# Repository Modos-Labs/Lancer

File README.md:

Lancer is the codename of our EPD laptop prototype.

# Specifications

The specification listed are preliminary and subject to change.

- SoC: Amlogic S922X (4x Cortex-A73 @ 2.2 GHz + 2x Cortex-A53 @ 2.0 GHz)
- RAM: 4GB DDR4 32bit
- SSD: User-replaceable M.2 SSD
- Network: 802.11n + BT4.0
- Screen: 13.3" 1600x1200 E-paper display via Caster EPDC (over MIPI DSI)
- Battery: Compatible with T4x battery
- Ports:
  - USB 2.0 Type-A Host x2
  - USB 2.0 Micro-B Device
  - USB Serial (Micro-B)
  - 10/100Mbps Ethernet
  - 3.5 mm Headphone Jack
  - 3.5 mm Line-In Jack
  - HDMI Output

# License

The hardware design is released under the CERN Open Source Hardware License strongly-reciprocal variant, CERN-OHL-S. A copy of the license is provided in the source repository. Additionally, user guide of the license is provided on ohwr.org.

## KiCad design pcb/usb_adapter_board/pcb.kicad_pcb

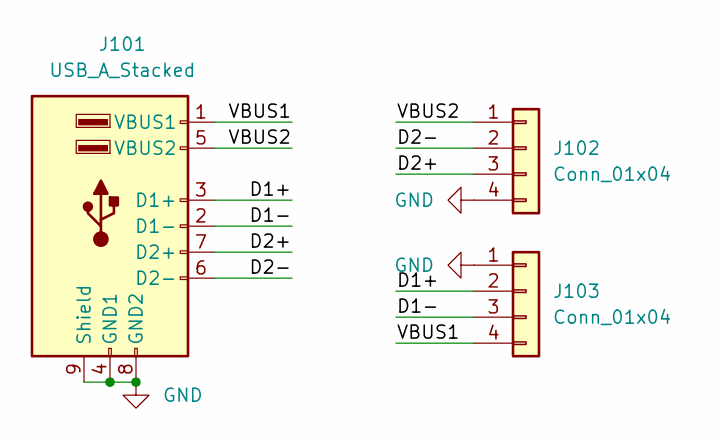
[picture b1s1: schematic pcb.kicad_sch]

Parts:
J101: USB_A_Stacked; USB_A_Wuerth_614008235023_Vertical_Stacked
J102, J103: Conn_01x04; PinHeader_1x04_P1.27mm_Horizontal_Alt

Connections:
/D1+: J101.3 (D1+), J103.2
/D1-: J101.2 (D1-), J103.3
/D2+: J101.7 (D2+), J102.3
/D2-: J101.6 (D2-), J102.2
/VBUS1: J101.1 (VBUS1), J103.4
/VBUS2: J101.5 (VBUS2), J102.1
GND: J101.4 (GND1), J101.8 (GND2), J101.9 (Shield), J102.4, J103.1

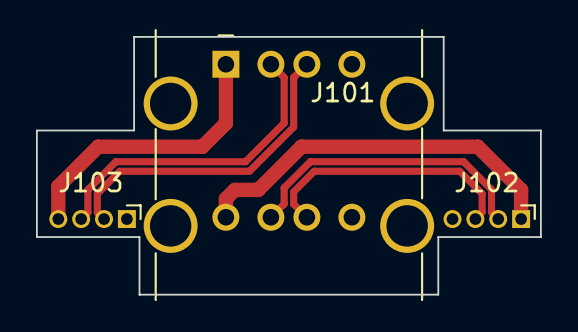
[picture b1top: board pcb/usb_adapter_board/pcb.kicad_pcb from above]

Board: 2 copper layers, 28.0 x 14.3 mm, 3 parts (0 on the bottom side), 7 nets.

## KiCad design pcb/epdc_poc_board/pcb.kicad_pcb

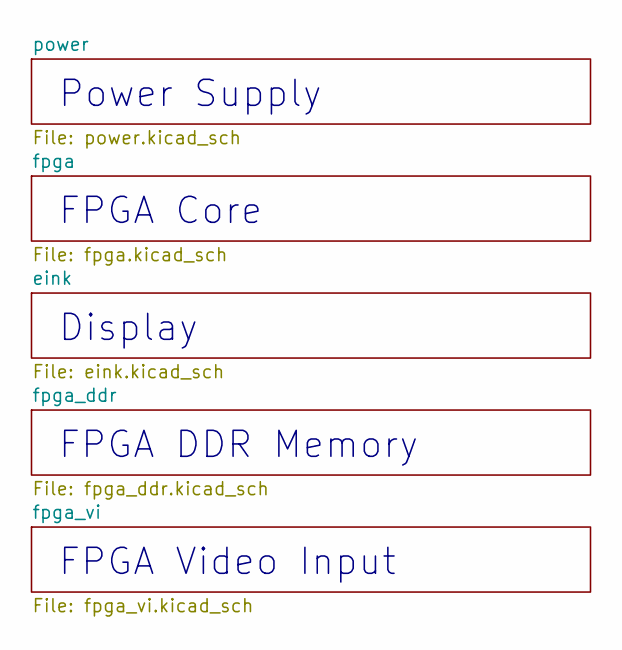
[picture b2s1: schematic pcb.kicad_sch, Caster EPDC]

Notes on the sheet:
Power Supply
FPGA Core
Display
FPGA DDR Memory
FPGA Video Input

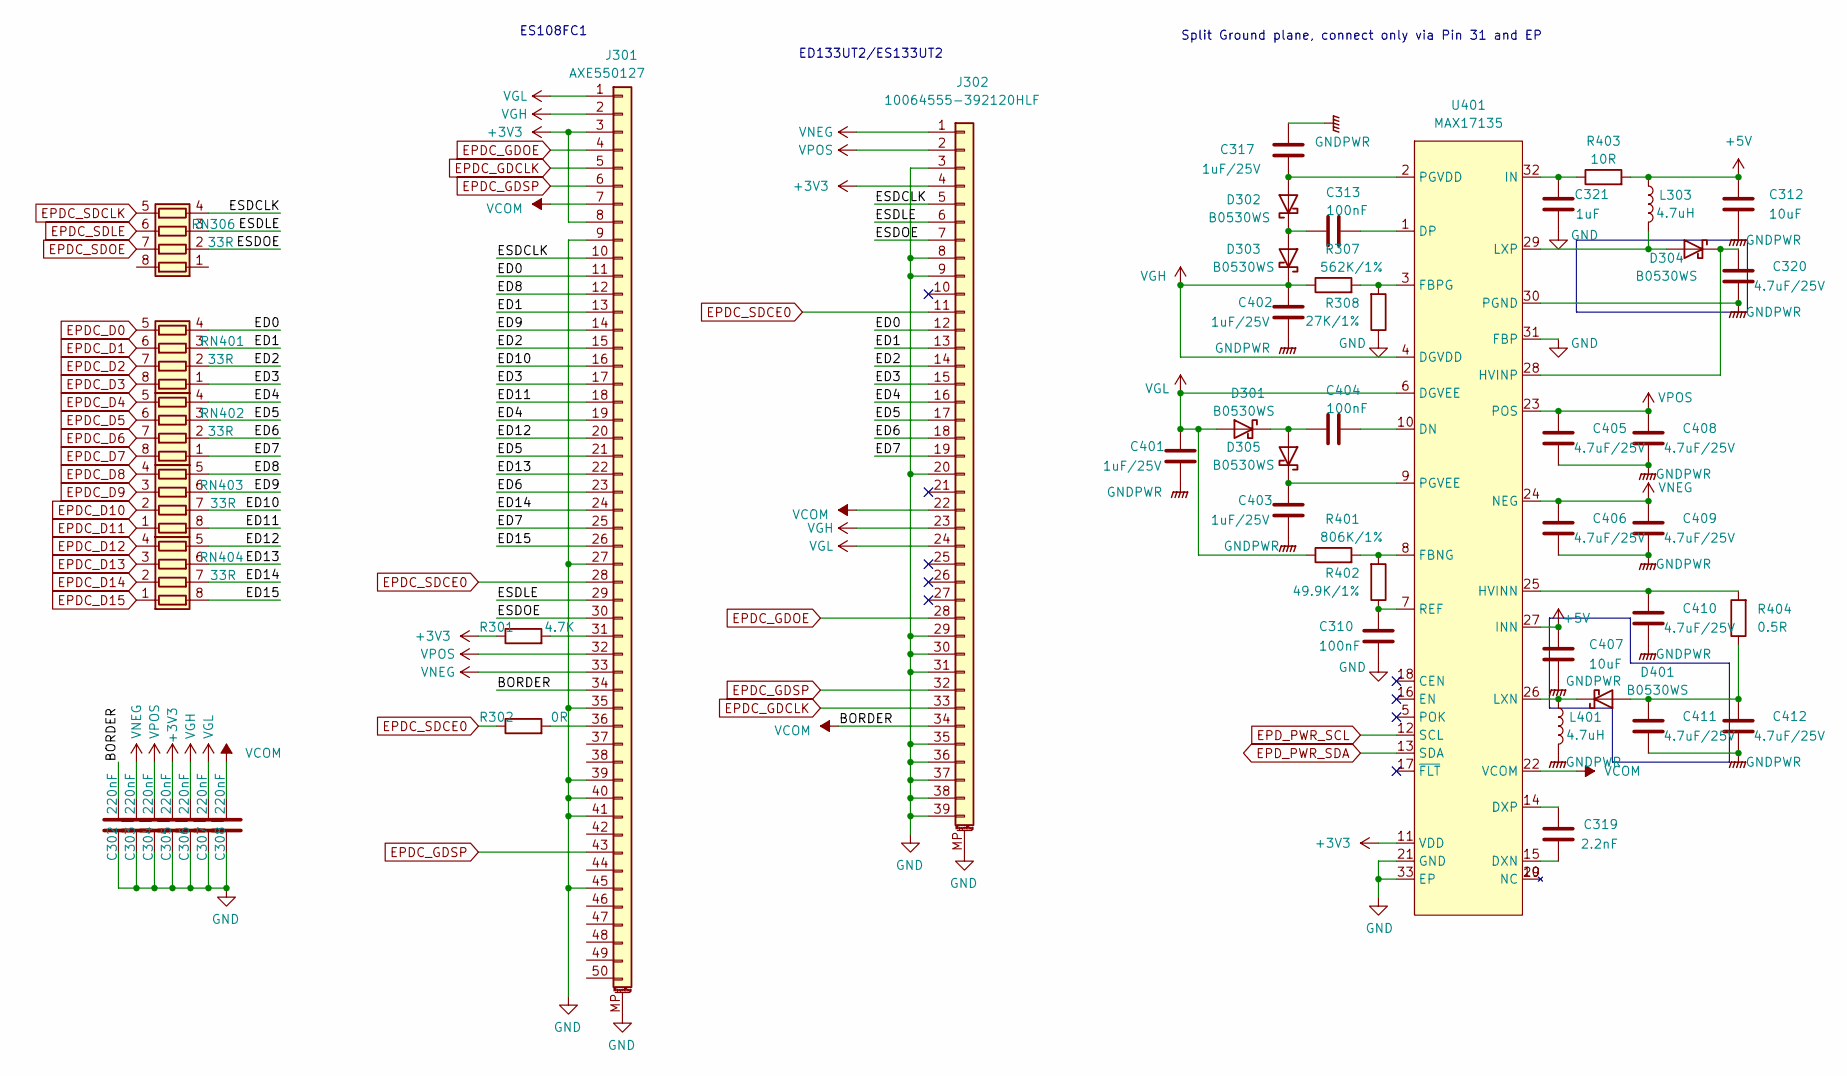
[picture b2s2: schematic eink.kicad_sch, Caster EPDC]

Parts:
C302, C303, C304, C305, C306, C307, C308: 220nF; C_0402_1005Metric; LCSC C880414
C310, C313, C404: 100nF; C_0402_1005Metric; LCSC C56392
C312, C407: 10uF; C_0603_1608Metric; LCSC C105490
C317, C401, C402, C403: 1uF/25V; C_0805_2012Metric; LCSC C111769
C319: 2.2nF; C_0402_1005Metric; LCSC C913886
C320, C405, C406, C408, C409, C410, C411, C412: 4.7uF/25V; C_0805_2012Metric; LCSC C105489
C321: 1uF; C_0402_1005Metric; LCSC C157353
D301, D302, D303, D304, D305, D401: B0530WS; D_SOD-323; LCSC C475612
J301: AXE550127
J302: 10064555-392120HLF; FCI_10064555-392120HLF; LCSC 609-10064555-392120HLFCT-ND
L303, L401: 4.7uH; L_1212; LCSC C340379
R301: 4.7K; R_0402_1005Metric; LCSC C105870
R302: 0R; R_0402_1005Metric; LCSC C60485
R307: 562K/1%; R_0402_1005Metric; LCSC C273337
R308: 27K/1%; R_0402_1005Metric; LCSC C138022
R401: 806K/1%; R_0402_1005Metric; LCSC C375495
R402: 49.9K/1%; R_0402_1005Metric; LCSC C137969
R403: 10R; R_0402_1005Metric; LCSC C137925
R404: 0.5R; R_0603_1608Metric; LCSC C45312
RN306, RN401, RN402, RN403, RN404: 33R; R_Array_Convex_4x0402; LCSC C148513
U401: MAX17135; QFN-32-1EP_5x5mm_P0.5mm_EP3.1x3.1mm_ThermalVias

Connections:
+3V3: C305.1, J301.3, J301.8, J302.4, R301.1, U401.11 (VDD); also elsewhere on the board
+5V: C312.2, C407.2, L303.1, R403.2, U401.27 (INN); also elsewhere on the board
/eink/ED0: J301.11, J302.12, RN401.4 (R4.1)
/eink/ED1: J301.13, J302.13, RN401.3 (R3.1)
/eink/ED2: J301.15, J302.14, RN401.2 (R2.1)
/eink/ED3: J301.17, J302.15, RN401.1 (R1.1)
/eink/ED4: J301.19, J302.16, RN402.4 (R4.1)
/eink/ED5: J301.21, J302.17, RN402.3 (R3.1)
/eink/ED6: J301.23, J302.18, RN402.2 (R2.1)
/eink/ED7: J301.25, J302.19, RN402.1 (R1.1)
/eink/ED8: J301.12, RN403.5 (R4.2)
/eink/ED9: J301.14, RN403.6 (R3.2)
/eink/ED10: J301.16, RN403.7 (R2.2)
/eink/ED11: J301.18, RN403.8 (R1.2)
/eink/ED12: J301.20, RN404.5 (R4.2)
/eink/ED13: J301.22, RN404.6 (R3.2)
/eink/ED14: J301.24, RN404.7 (R2.2)
/eink/ED15: J301.26, RN404.8 (R1.2)
/eink/ESDCLK: J301.10, J302.5, RN306.4 (R4.1)
/eink/ESDLE: J301.29, J302.6, RN306.3 (R3.1)
/eink/ESDOE: J301.30, J302.7, RN306.2 (R2.1)
EPDC_D0: RN401.5 (R4.2); also elsewhere on the board
EPDC_D1: RN401.6 (R3.2); also elsewhere on the board
EPDC_D2: RN401.7 (R2.2); also elsewhere on the board
EPDC_D3: RN401.8 (R1.2); also elsewhere on the board
EPDC_D4: RN402.5 (R4.2); also elsewhere on the board
EPDC_D5: RN402.6 (R3.2); also elsewhere on the board
EPDC_D6: RN402.7 (R2.2); also elsewhere on the board
EPDC_D7: RN402.8 (R1.2); also elsewhere on the board
EPDC_D8: RN403.4 (R4.1); also elsewhere on the board
EPDC_D9: RN403.3 (R3.1); also elsewhere on the board
EPDC_D10: RN403.2 (R2.1); also elsewhere on the board
EPDC_D11: RN403.1 (R1.1); also elsewhere on the board
EPDC_D12: RN404.4 (R4.1); also elsewhere on the board
EPDC_D13: RN404.3 (R3.1); also elsewhere on the board
EPDC_D14: RN404.2 (R2.1); also elsewhere on the board
EPDC_D15: RN404.1 (R1.1); also elsewhere on the board
EPDC_GDCLK: J301.5, J302.33; also elsewhere on the board
EPDC_GDOE: J301.4, J302.28; also elsewhere on the board
EPDC_GDSP: J301.6, J301.43, J302.32; also elsewhere on the board
EPDC_SDCE0: J301.28, J302.11, R302.1; also elsewhere on the board
EPDC_SDCLK: RN306.5 (R4.2); also elsewhere on the board
EPDC_SDLE: RN306.6 (R3.2); also elsewhere on the board
EPDC_SDOE: RN306.7 (R2.2); also elsewhere on the board
EPD_PWR_SCL: U401.12 (SCL); also elsewhere on the board
EPD_PWR_SDA: U401.13 (SDA); also elsewhere on the board
GND: C302.2, C303.2, C304.2, C305.2, C306.2, C307.2, C308.2, C310.1, C321.1, J301.9, J301.27, J301.35, J301.39, J301.40, J301.41, J301.45, J301.MP (MountPin), J302.3, J302.8, J302.9, J302.20, J302.29, J302.30, J302.31, J302.35, J302.36, J302.37, J302.38, J302.39, J302.MP (MountPin), R308.1, U401.21 (GND), U401.31 (FBP), U401.33 (EP); also elsewhere on the board
GNDPWR: C312.1, C317.2, C320.1, C401.1, C402.1, C403.1, C405.1, C406.1, C407.1, C408.1, C409.1, C410.1, C411.1, C412.1, L401.2, U401.30 (PGND)
unnamed: C310.2, R402.1, U401.7 (REF)
unnamed: C313.1, D302.1 (K), D303.2 (A)
unnamed: C313.2, U401.1 (DP)
unnamed: C317.1, D302.2 (A), U401.2 (PGVDD)
unnamed: C319.1, U401.15 (DXN)
unnamed: C319.2, U401.14 (DXP)
unnamed: C320.2, D304.1 (K), U401.28 (HVINP)
unnamed: C321.2, R403.1, U401.32 (IN)
unnamed: C403.2, D305.1 (K), U401.9 (PGVEE)
unnamed: C404.1, D301.1 (K), D305.2 (A)
unnamed: C404.2, U401.10 (DN)
unnamed: C410.2, R404.2, U401.25 (HVINN)
unnamed: C411.2, C412.2, D401.2 (A), R404.1
unnamed: D304.2 (A), L303.2, U401.29 (LXP)
unnamed: D401.1 (K), L401.1, U401.26 (LXN)
unnamed: J301.31, R301.2
unnamed: J301.36, R302.2
unnamed: R307.2, R308.2, U401.3 (FBPG)
unnamed: R401.2, R402.2, U401.8 (FBNG)
VCOM: C302.1, C308.1, J301.7, J301.34, J302.22, J302.34, U401.22 (VCOM)
VGH: C306.1, C402.2, D303.1 (K), J301.2, J302.23, R307.1, U401.4 (DGVDD)
VGL: C307.1, C401.2, D301.2 (A), J301.1, J302.24, R401.1, U401.6 (DGVEE)
VNEG: C303.1, C406.2, C409.2, J301.33, J302.1, U401.24 (NEG)
VPOS: C304.1, C405.2, C408.2, J301.32, J302.2, U401.23 (POS)

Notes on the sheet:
ES108FC1
ED133UT2/ES133UT2
Split Ground plane, connect only via Pin 31 and EP

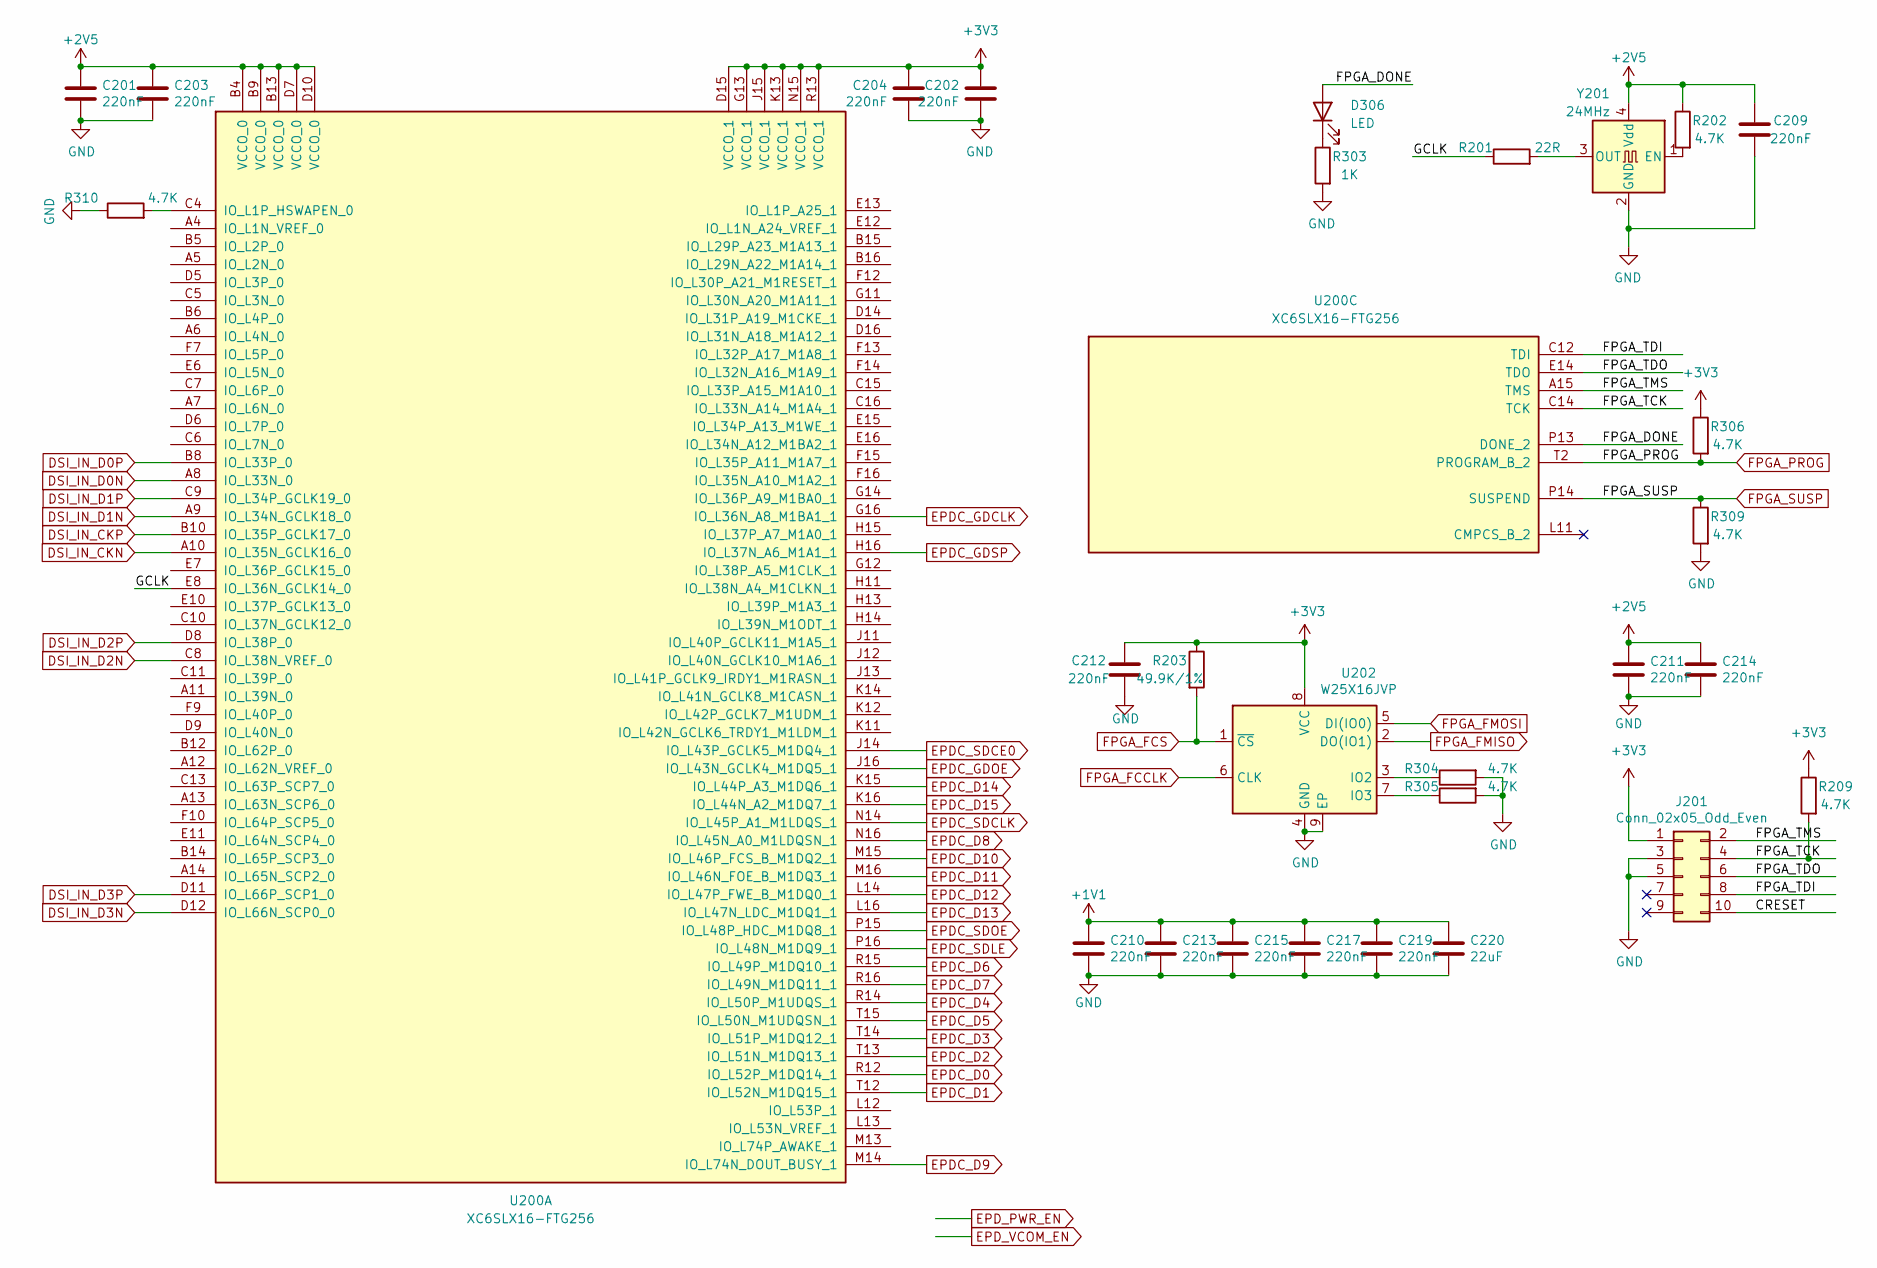
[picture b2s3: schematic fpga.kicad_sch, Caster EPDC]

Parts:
C201, C202, C203, C204, C209, C210, C211, C212, C213, C214, C215, C217, C219: 220nF; C_0402_1005Metric; LCSC C880414
C220: 22uF; C_0603_1608Metric; LCSC C94018
D306: LED; LED_0603_1608Metric; LCSC C90692
J201: Conn_02x05_Odd_Even; PinHeader_2x05_P1.27mm_Vertical_SMD
R201: 22R; R_0402_1005Metric; LCSC C93929
R202, R209, R304, R305, R306, R309, R310: 4.7K; R_0402_1005Metric; LCSC C105870
R203: 49.9K/1%; R_0402_1005Metric; LCSC C137969
R303: 1K; R_0402_1005Metric; LCSC C105637
U200: XC6SLX16-FTG256; BGA-256_14.0x14.0mm_Layout16x16_P0.8mm_Ball0.45mm_Pad0.32mm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; LCSC C39313
U202: W25X16JVP; WSON-8-1EP_6x5mm_P1.27mm_EP3.4x4.3mm; LCSC C571260
Y201: 24MHz; Oscillator_SMD_Abracon_ASE-4Pin_3.2x2.5mm; LCSC C252339

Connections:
+1V1: C210.1, C213.1, C215.1, C217.1, C219.1, C220.1; also elsewhere on the board
+2V5: C201.1, C203.1, C209.2, C211.1, C214.1, R202.1, U200.B4 (VCCO_0), U200.B9 (VCCO_0), U200.B13 (VCCO_0), U200.D7 (VCCO_0), U200.D10 (VCCO_0), Y201.4 (Vdd); also elsewhere on the board
+3V3: C202.1, C204.1, C212.2, J201.1, R203.1, R209.1, R306.1, U200.D15 (VCCO_1), U200.G13 (VCCO_1), U200.J15 (VCCO_1), U200.K13 (VCCO_1), U200.N15 (VCCO_1), U200.R13 (VCCO_1), U202.8 (VCC); also elsewhere on the board
/fpga/CRESET: J201.10
/fpga/FPGA_DONE: D306.2 (A), U200.P13 (DONE_2)
/fpga/FPGA_TCK: J201.4, R209.2, U200.C14 (TCK)
/fpga/FPGA_TDI: J201.8, U200.C12 (TDI)
/fpga/FPGA_TDO: J201.6, U200.E14 (TDO)
/fpga/FPGA_TMS: J201.2, U200.A15 (TMS)
/fpga/GCLK: R201.1, U200.E8 (IO_L36N_GCLK14_0)
DSI_IN_CKN: U200.A10 (IO_L35N_GCLK16_0); also elsewhere on the board
DSI_IN_CKP: U200.B10 (IO_L35P_GCLK17_0); also elsewhere on the board
DSI_IN_D0N: U200.A8 (IO_L33N_0); also elsewhere on the board
DSI_IN_D0P: U200.B8 (IO_L33P_0); also elsewhere on the board
DSI_IN_D1N: U200.A9 (IO_L34N_GCLK18_0); also elsewhere on the board
DSI_IN_D1P: U200.C9 (IO_L34P_GCLK19_0); also elsewhere on the board
DSI_IN_D2N: U200.C8 (IO_L38N_VREF_0); also elsewhere on the board
DSI_IN_D2P: U200.D8 (IO_L38P_0); also elsewhere on the board
DSI_IN_D3N: U200.D12 (IO_L66N_SCP0_0); also elsewhere on the board
DSI_IN_D3P: U200.D11 (IO_L66P_SCP1_0); also elsewhere on the board
EPDC_D0: U200.R12 (IO_L52P_M1DQ14_1); also elsewhere on the board
EPDC_D1: U200.T12 (IO_L52N_M1DQ15_1); also elsewhere on the board
EPDC_D2: U200.T13 (IO_L51N_M1DQ13_1); also elsewhere on the board
EPDC_D3: U200.T14 (IO_L51P_M1DQ12_1); also elsewhere on the board
EPDC_D4: U200.R14 (IO_L50P_M1UDQS_1); also elsewhere on the board
EPDC_D5: U200.T15 (IO_L50N_M1UDQSN_1); also elsewhere on the board
EPDC_D6: U200.R15 (IO_L49P_M1DQ10_1); also elsewhere on the board
EPDC_D7: U200.R16 (IO_L49N_M1DQ11_1); also elsewhere on the board
EPDC_D8: U200.N16 (IO_L45N_A0_M1LDQSN_1); also elsewhere on the board
EPDC_D9: U200.M14 (IO_L74N_DOUT_BUSY_1); also elsewhere on the board
EPDC_D10: U200.M15 (IO_L46P_FCS_B_M1DQ2_1); also elsewhere on the board
EPDC_D11: U200.M16 (IO_L46N_FOE_B_M1DQ3_1); also elsewhere on the board
EPDC_D12: U200.L14 (IO_L47P_FWE_B_M1DQ0_1); also elsewhere on the board
EPDC_D13: U200.L16 (IO_L47N_LDC_M1DQ1_1); also elsewhere on the board
EPDC_D14: U200.K15 (IO_L44P_A3_M1DQ6_1); also elsewhere on the board
EPDC_D15: U200.K16 (IO_L44N_A2_M1DQ7_1); also elsewhere on the board
EPDC_GDCLK: U200.G16 (IO_L36N_A8_M1BA1_1); also elsewhere on the board
EPDC_GDOE: U200.J16 (IO_L43N_GCLK4_M1DQ5_1); also elsewhere on the board
EPDC_GDSP: U200.H16 (IO_L37N_A6_M1A1_1); also elsewhere on the board
EPDC_SDCE0: U200.J14 (IO_L43P_GCLK5_M1DQ4_1); also elsewhere on the board
EPDC_SDCLK: U200.N14 (IO_L45P_A1_M1LDQS_1); also elsewhere on the board
EPDC_SDLE: U200.P16 (IO_L48N_M1DQ9_1); also elsewhere on the board
EPDC_SDOE: U200.P15 (IO_L48P_HDC_M1DQ8_1); also elsewhere on the board
FPGA_FCCLK: U202.6 (CLK); also elsewhere on the board
FPGA_FCS: R203.2, U202.1 (~CS); also elsewhere on the board
FPGA_FMISO: U202.2 (DO(IO1)); also elsewhere on the board
FPGA_FMOSI: U202.5 (DI(IO0)); also elsewhere on the board
FPGA_PROG: R306.2, U200.T2 (PROGRAM_B_2); also elsewhere on the board
FPGA_SUSP: R309.1, U200.P14 (SUSPEND); also elsewhere on the board
GND: C201.2, C202.2, C203.2, C204.2, C209.1, C210.2, C211.2, C212.1, C213.2, C214.2, C215.2, C217.2, C219.2, C220.2, J201.3, J201.5, R303.2, R304.2, R305.2, R309.2, R310.1, U202.4 (GND), U202.9 (EP), Y201.2 (GND); also elsewhere on the board
unnamed: D306.1 (K), R303.1
unnamed: R201.2, Y201.3 (OUT)
unnamed: R202.2, Y201.1 (EN)
unnamed: R304.1, U202.3 (IO2)
unnamed: R305.1, U202.7 (IO3)
unnamed: R310.2, U200.C4 (IO_L1P_HSWAPEN_0)

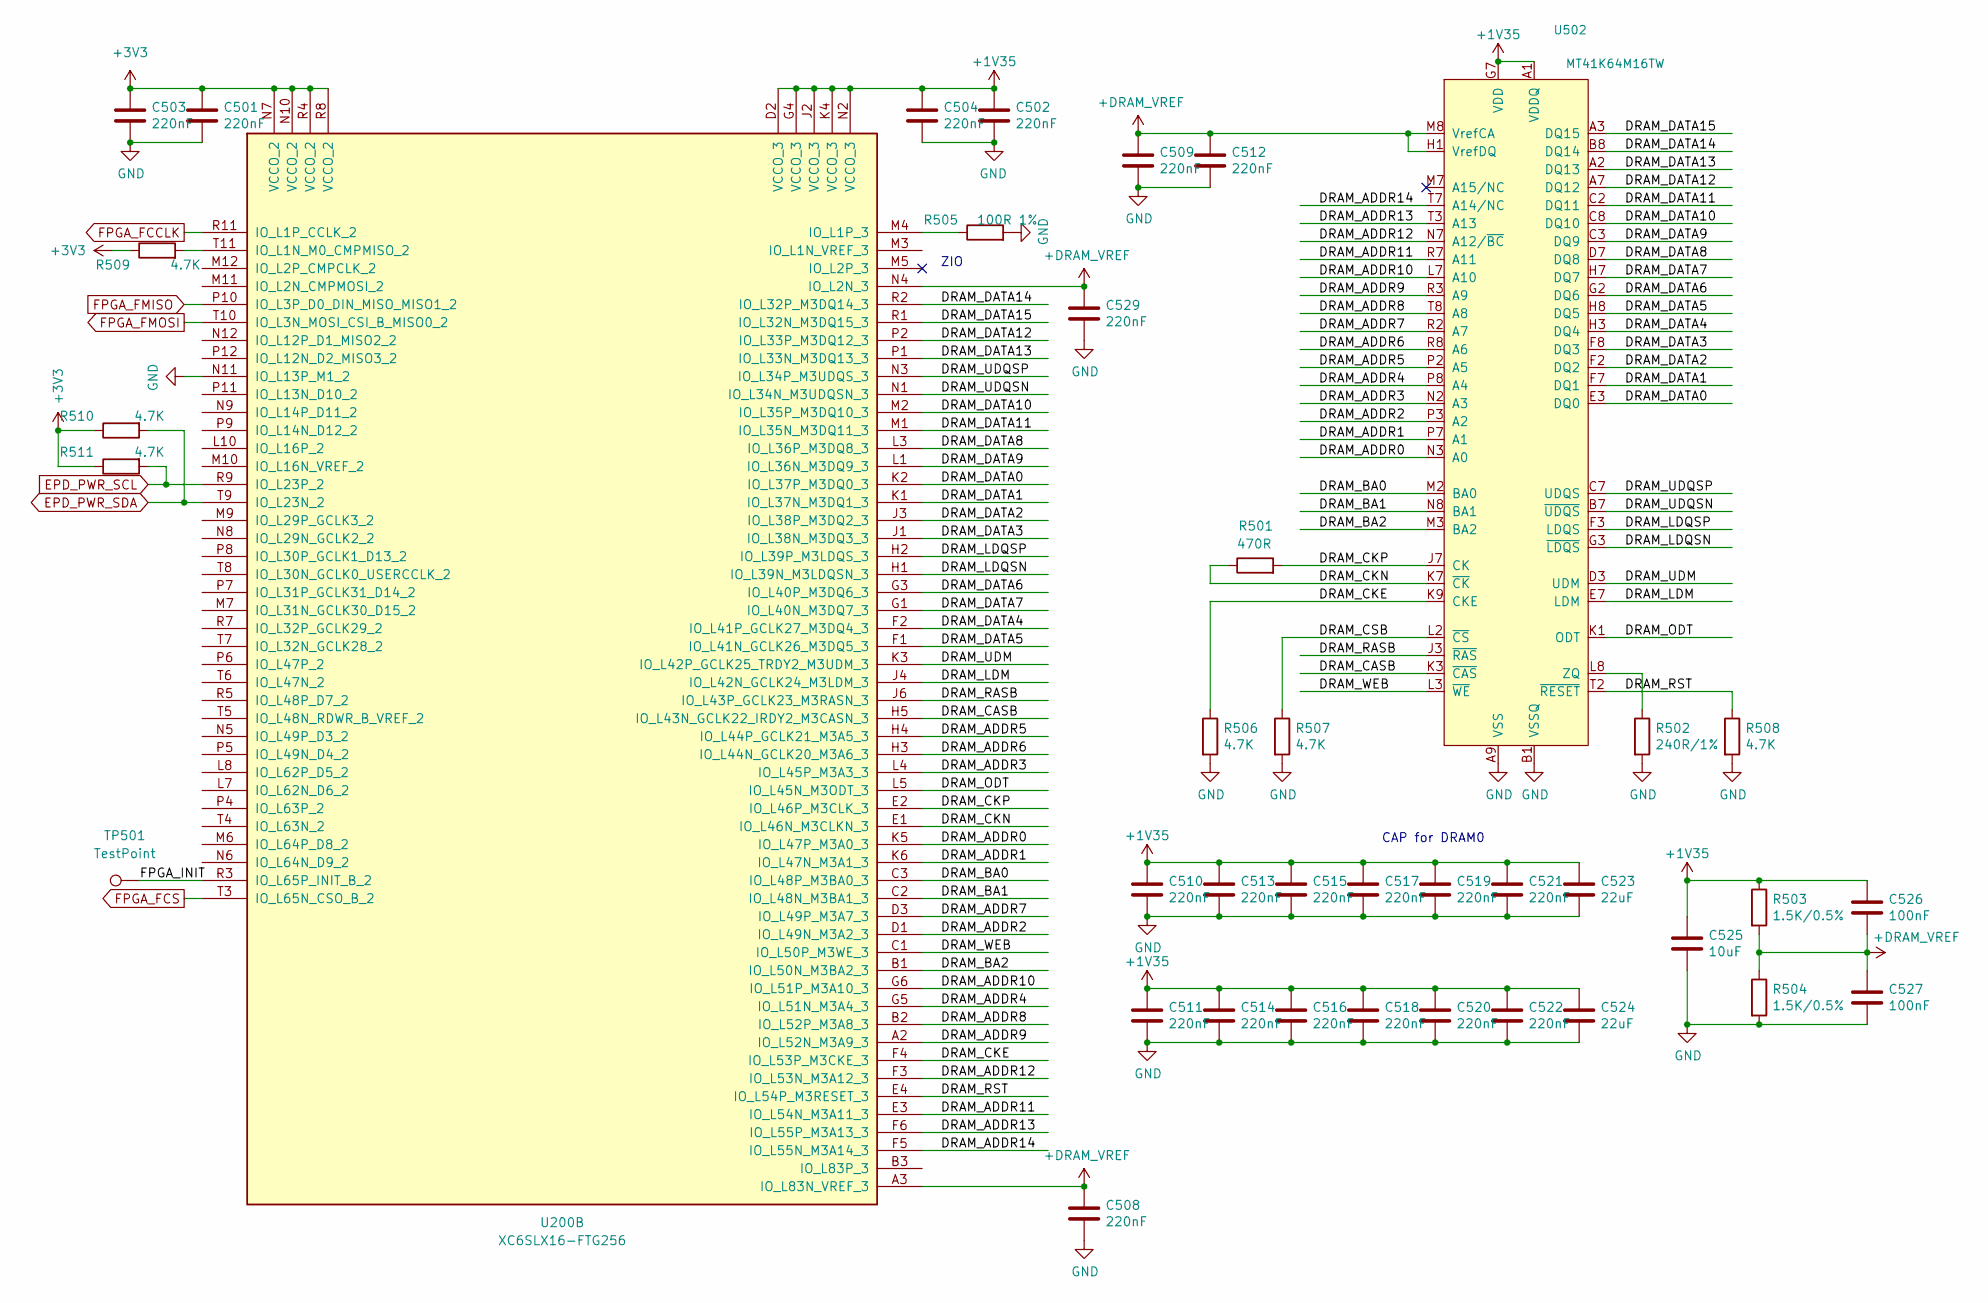
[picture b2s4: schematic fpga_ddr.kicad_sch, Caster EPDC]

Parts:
C501, C502, C503, C504, C508, C509, C510, C511, C512, C513, C514, C515, C516, C517, C518, C519, C520, C521, C522, C529: 220nF; C_0402_1005Metric; LCSC C880414
C523, C524: 22uF; C_0603_1608Metric; LCSC C94018
C525: 10uF; C_0603_1608Metric; LCSC C105490
C526, C527: 100nF; C_0402_1005Metric; LCSC C56392
R501: 470R; R_0402_1005Metric; LCSC C114877
R502: 240R/1%; R_0402_1005Metric; LCSC C114755
R503, R504: 1.5K/0.5%; R_0402_1005Metric; LCSC C226693
R505: 100R 1%; R_0402_1005Metric; LCSC C106232
R506, R507, R508, R509, R510, R511: 4.7K; R_0402_1005Metric; LCSC C105870
TP501: TestPoint; TestPoint_Pad_D1.0mm
U200: XC6SLX16-FTG256; BGA-256_14.0x14.0mm_Layout16x16_P0.8mm_Ball0.45mm_Pad0.32mm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; LCSC C39313
U502: MT41K64M16TW; BGA-96_9.0x14.0mm_P0.8mm; LCSC C524855

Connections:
+1V35: C502.1, C504.1, C510.1, C511.1, C513.1, C514.1, C515.1, C516.1, C517.1, C518.1, C519.1, C520.1, C521.1, C522.1, C523.1, C524.1, C525.1, C526.1, R503.1, U200.D2 (VCCO_3), U200.G4 (VCCO_3), U200.J2 (VCCO_3), U200.K4 (VCCO_3), U200.N2 (VCCO_3), U502.A1 (VDDQ), U502.A8 (VDDQ), U502.B2 (VDD), U502.C1 (VDDQ), U502.C9 (VDDQ), U502.D2 (VDDQ), U502.D9 (VDD), U502.E9 (VDDQ), U502.F1 (VDDQ), U502.G7 (VDD), U502.H2 (VDDQ), U502.H9 (VDDQ), U502.K2 (VDD), U502.K8 (VDD), U502.N1 (VDD), U502.N9 (VDD), U502.R1 (VDD), U502.R9 (VDD); also elsewhere on the board
+3V3: C501.1, C503.1, R509.1, R510.1, R511.1, U200.N7 (VCCO_2), U200.N10 (VCCO_2), U200.R4 (VCCO_2), U200.R8 (VCCO_2); also elsewhere on the board
+DRAM_VREF: C508.1, C509.1, C512.1, C526.2, C527.1, C529.1, R503.2, R504.1, U200.A3 (IO_L83N_VREF_3), U200.N4 (IO_L2N_3), U502.H1 (VrefDQ), U502.M8 (VrefCA)
/fpga_ddr/DRAM_ADDR0: U200.K5 (IO_L47P_M3A0_3), U502.N3 (A0)
/fpga_ddr/DRAM_ADDR1: U200.K6 (IO_L47N_M3A1_3), U502.P7 (A1)
/fpga_ddr/DRAM_ADDR2: U200.D1 (IO_L49N_M3A2_3), U502.P3 (A2)
/fpga_ddr/DRAM_ADDR3: U200.L4 (IO_L45P_M3A3_3), U502.N2 (A3)
/fpga_ddr/DRAM_ADDR4: U200.G5 (IO_L51N_M3A4_3), U502.P8 (A4)
/fpga_ddr/DRAM_ADDR5: U200.H4 (IO_L44P_GCLK21_M3A5_3), U502.P2 (A5)
/fpga_ddr/DRAM_ADDR6: U200.H3 (IO_L44N_GCLK20_M3A6_3), U502.R8 (A6)
/fpga_ddr/DRAM_ADDR7: U200.D3 (IO_L49P_M3A7_3), U502.R2 (A7)
/fpga_ddr/DRAM_ADDR8: U200.B2 (IO_L52P_M3A8_3), U502.T8 (A8)
/fpga_ddr/DRAM_ADDR9: U200.A2 (IO_L52N_M3A9_3), U502.R3 (A9)
/fpga_ddr/DRAM_ADDR10: U200.G6 (IO_L51P_M3A10_3), U502.L7 (A10)
/fpga_ddr/DRAM_ADDR11: U200.E3 (IO_L54N_M3A11_3), U502.R7 (A11)
/fpga_ddr/DRAM_ADDR12: U200.F3 (IO_L53N_M3A12_3), U502.N7 (A12/~BC)
/fpga_ddr/DRAM_ADDR13: U200.F6 (IO_L55P_M3A13_3), U502.T3 (A13)
/fpga_ddr/DRAM_ADDR14: U200.F5 (IO_L55N_M3A14_3), U502.T7 (A14/NC)
/fpga_ddr/DRAM_BA0: U200.C3 (IO_L48P_M3BA0_3), U502.M2 (BA0)
/fpga_ddr/DRAM_BA1: U200.C2 (IO_L48N_M3BA1_3), U502.N8 (BA1)
/fpga_ddr/DRAM_BA2: U200.B1 (IO_L50N_M3BA2_3), U502.M3 (BA2)
/fpga_ddr/DRAM_CASB: U200.H5 (IO_L43N_GCLK22_IRDY2_M3CASN_3), U502.K3 (~CAS)
/fpga_ddr/DRAM_CKE: R506.1, U200.F4 (IO_L53P_M3CKE_3), U502.K9 (CKE)
/fpga_ddr/DRAM_CKN: R501.1, U200.E1 (IO_L46N_M3CLKN_3), U502.K7 (~CK)
/fpga_ddr/DRAM_CKP: R501.2, U200.E2 (IO_L46P_M3CLK_3), U502.J7 (CK)
/fpga_ddr/DRAM_CSB: R507.1, U502.L2 (~CS)
/fpga_ddr/DRAM_DATA0: U200.K2 (IO_L37P_M3DQ0_3), U502.E3 (DQ0)
/fpga_ddr/DRAM_DATA1: U200.K1 (IO_L37N_M3DQ1_3), U502.F7 (DQ1)
/fpga_ddr/DRAM_DATA2: U200.J3 (IO_L38P_M3DQ2_3), U502.F2 (DQ2)
/fpga_ddr/DRAM_DATA3: U200.J1 (IO_L38N_M3DQ3_3), U502.F8 (DQ3)
/fpga_ddr/DRAM_DATA4: U200.F2 (IO_L41P_GCLK27_M3DQ4_3), U502.H3 (DQ4)
/fpga_ddr/DRAM_DATA5: U200.F1 (IO_L41N_GCLK26_M3DQ5_3), U502.H8 (DQ5)
/fpga_ddr/DRAM_DATA6: U200.G3 (IO_L40P_M3DQ6_3), U502.G2 (DQ6)
/fpga_ddr/DRAM_DATA7: U200.G1 (IO_L40N_M3DQ7_3), U502.H7 (DQ7)
/fpga_ddr/DRAM_DATA8: U200.L3 (IO_L36P_M3DQ8_3), U502.D7 (DQ8)
/fpga_ddr/DRAM_DATA9: U200.L1 (IO_L36N_M3DQ9_3), U502.C3 (DQ9)
/fpga_ddr/DRAM_DATA10: U200.M2 (IO_L35P_M3DQ10_3), U502.C8 (DQ10)
/fpga_ddr/DRAM_DATA11: U200.M1 (IO_L35N_M3DQ11_3), U502.C2 (DQ11)
/fpga_ddr/DRAM_DATA12: U200.P2 (IO_L33P_M3DQ12_3), U502.A7 (DQ12)
/fpga_ddr/DRAM_DATA13: U200.P1 (IO_L33N_M3DQ13_3), U502.A2 (DQ13)
/fpga_ddr/DRAM_DATA14: U200.R2 (IO_L32P_M3DQ14_3), U502.B8 (DQ14)
/fpga_ddr/DRAM_DATA15: U200.R1 (IO_L32N_M3DQ15_3), U502.A3 (DQ15)
/fpga_ddr/DRAM_LDM: U200.J4 (IO_L42N_GCLK24_M3LDM_3), U502.E7 (LDM)
/fpga_ddr/DRAM_LDQSN: U200.H1 (IO_L39N_M3LDQSN_3), U502.G3 (~LDQS)
/fpga_ddr/DRAM_LDQSP: U200.H2 (IO_L39P_M3LDQS_3), U502.F3 (LDQS)
/fpga_ddr/DRAM_ODT: U200.L5 (IO_L45N_M3ODT_3), U502.K1 (ODT)
/fpga_ddr/DRAM_RASB: U200.J6 (IO_L43P_GCLK23_M3RASN_3), U502.J3 (~RAS)
/fpga_ddr/DRAM_RST: R508.1, U200.E4 (IO_L54P_M3RESET_3), U502.T2 (~RESET)
/fpga_ddr/DRAM_UDM: U200.K3 (IO_L42P_GCLK25_TRDY2_M3UDM_3), U502.D3 (UDM)
/fpga_ddr/DRAM_UDQSN: U200.N1 (IO_L34N_M3UDQSN_3), U502.B7 (~UDQS)
/fpga_ddr/DRAM_UDQSP: U200.N3 (IO_L34P_M3UDQS_3), U502.C7 (UDQS)
/fpga_ddr/DRAM_WEB: U200.C1 (IO_L50P_M3WE_3), U502.L3 (~WE)
/fpga_ddr/FPGA_INIT: TP501.1, U200.R3 (IO_L65P_INIT_B_2)
EPD_PWR_SCL: R511.2, U200.R9 (IO_L23P_2); also elsewhere on the board
EPD_PWR_SDA: R510.2, U200.T9 (IO_L23N_2); also elsewhere on the board
FPGA_FCCLK: U200.R11 (IO_L1P_CCLK_2); also elsewhere on the board
FPGA_FCS: U200.T3 (IO_L65N_CSO_B_2); also elsewhere on the board
FPGA_FMISO: U200.P10 (IO_L3P_D0_DIN_MISO_MISO1_2); also elsewhere on the board
FPGA_FMOSI: U200.T10 (IO_L3N_MOSI_CSI_B_MISO0_2); also elsewhere on the board
GND: C501.2, C502.2, C503.2, C504.2, C508.2, C509.2, C510.2, C511.2, C512.2, C513.2, C514.2, C515.2, C516.2, C517.2, C518.2, C519.2, C520.2, C521.2, C522.2, C523.2, C524.2, C525.2, C527.2, C529.2, R502.2, R504.2, R505.2, R506.2, R507.2, R508.2, U200.N11 (IO_L13P_M1_2), U502.A9 (VSS), U502.B1 (VSSQ), U502.B3 (VSS), U502.B9 (VSSQ), U502.D1 (VSSQ), U502.D8 (VSSQ), U502.E1 (VSS), U502.E2 (VSSQ), U502.E8 (VSSQ), U502.F9 (VSSQ), U502.G1 (VSSQ), U502.G8 (VSS), U502.G9 (VSSQ), U502.J2 (VSS), U502.J8 (VSS), U502.M1 (VSS), U502.M9 (VSS), U502.P1 (VSS), U502.P9 (VSS), U502.T1 (VSS), U502.T9 (VSS); also elsewhere on the board
unnamed: R502.1, U502.L8 (ZQ)
unnamed: R505.1, U200.M4 (IO_L1P_3)
unnamed: R509.2, U200.T11 (IO_L1N_M0_CMPMISO_2)

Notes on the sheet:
ZIO
CAP for DRAM0

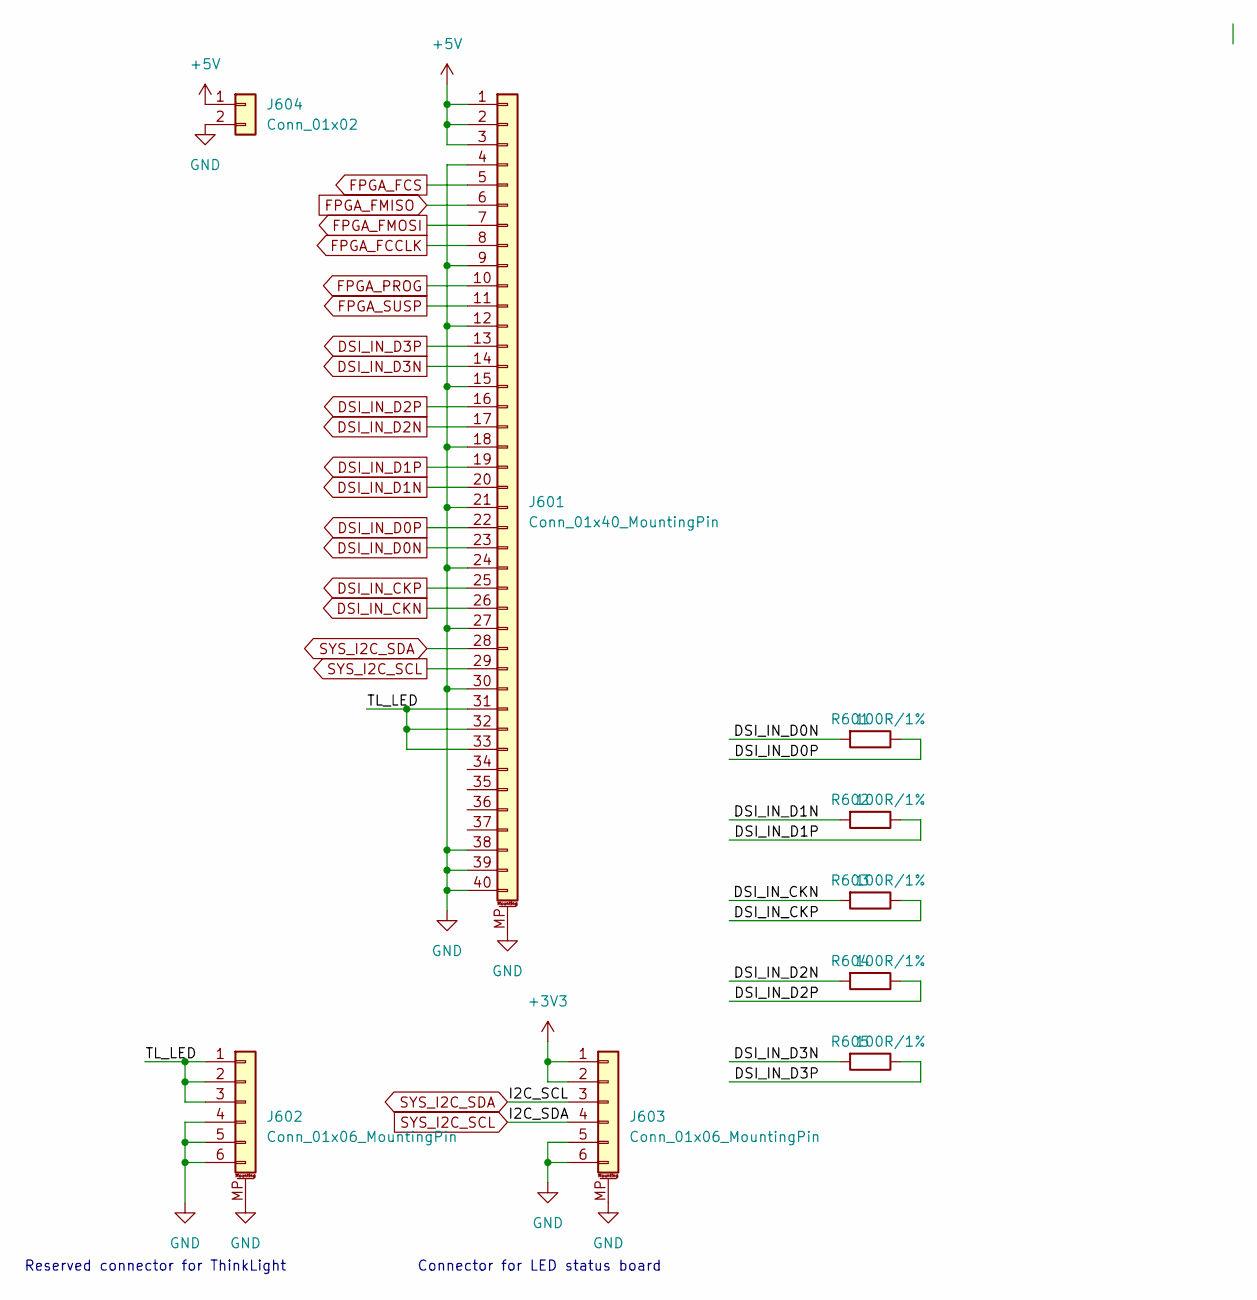
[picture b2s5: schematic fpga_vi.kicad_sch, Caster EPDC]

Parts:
J601: Conn_01x40_MountingPin; Hirose_FH12-40S-0.5SH_1x40-1MP_P0.50mm_Horizontal; LCSC C376071
J602, J603: Conn_01x06_MountingPin; Hirose_FH12-6S-0.5SH_1x06-1MP_P0.50mm_Horizontal; LCSC C283139
J604: Conn_01x02; PinHeader_1x02_P2.54mm_Vertical
R601, R602, R603, R604, R605: 100R/1%; R_0402_1005Metric; LCSC C106232

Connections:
+3V3: J603.1, J603.2; also elsewhere on the board
+5V: J601.1, J601.2, J601.3, J604.1; also elsewhere on the board
/fpga_vi/TL_LED: J601.31, J601.32, J601.33, J602.1, J602.2, J602.3
DSI_IN_CKN: J601.26, R603.2; also elsewhere on the board
DSI_IN_CKP: J601.25, R603.1; also elsewhere on the board
DSI_IN_D0N: J601.23, R601.2; also elsewhere on the board
DSI_IN_D0P: J601.22, R601.1; also elsewhere on the board
DSI_IN_D1N: J601.20, R602.2; also elsewhere on the board
DSI_IN_D1P: J601.19, R602.1; also elsewhere on the board
DSI_IN_D2N: J601.17, R604.2; also elsewhere on the board
DSI_IN_D2P: J601.16, R604.1; also elsewhere on the board
DSI_IN_D3N: J601.14, R605.2; also elsewhere on the board
DSI_IN_D3P: J601.13, R605.1; also elsewhere on the board
FPGA_FCCLK: J601.8; also elsewhere on the board
FPGA_FCS: J601.5; also elsewhere on the board
FPGA_FMISO: J601.6; also elsewhere on the board
FPGA_FMOSI: J601.7; also elsewhere on the board
FPGA_PROG: J601.10; also elsewhere on the board
FPGA_SUSP: J601.11; also elsewhere on the board
GND: J601.4, J601.9, J601.12, J601.15, J601.18, J601.21, J601.24, J601.27, J601.30, J601.38, J601.39, J601.40, J601.MP (MountPin), J602.4, J602.5, J602.6, J602.MP (MountPin), J603.5, J603.6, J603.MP (MountPin), J604.2; also elsewhere on the board
SYS_I2C_SCL: J601.29, J603.4
SYS_I2C_SDA: J601.28, J603.3

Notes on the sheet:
Reserved connector for ThinkLight
Connector for LED status board

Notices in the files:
pcb/epdc_poc_board/eink.kicad_sch:
Copyright 2021 Modos / Engineer: Wenting Zhang
pcb/epdc_poc_board/pcb.kicad_pcb:
(C) 2021 MODOS
pcb/mainboard/pcb.kicad_sch:
Copyright Modos 2021. / Engineer: Wenting Zhang
This source describes Open Hardware and is licensed under the CERN-OHL-S v2.
